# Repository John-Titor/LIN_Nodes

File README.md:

Firmware and PCB designs for various LIN network nodes intended for retrofitting older vehicles.

```
boards/
    Eagle schematic and PCB files.

common/
    Protocol definitions and generator.

Documentation/
    Datasheets for various parts used in the design.

lintool
    Host-side configuration tool. Talks to the usb_link hardware.

nodes/
    All of the nodes in this part of the tree are based on the Atmel ATTiny167.

    bl_core/
        LIN bootloader core, consumed by bl_installer.

    bl_installer/
        Bootloader installer; flashed onto a fresh board this will install the
        bootloader.

        The installed bootloader comes up on NAD 32 and can be flashed with lintool
        by explicitly supplying the node address and firmware file.

        lintool update -n 32 <path-to-fw-file>

        Only one node can be in this 'recovery' mode on the network when doing this.

    lib/
        Shared code.

    master/
        Network master node. Supports 7 switch-to-battery and 14 switch-to-ground
        inputs. 4 of the switch-to-ground inputs can also be 0-5V voltage inputs,
        with optional 2 or 16mA current sources for measuring resistive sensors.

    power_v3/
        5-output power switching node using Freescale smart high-side switches.
        Board limited to 5.5A, but code should work with the 10A device as well.
        Outputs support PWM, current monitoring, open- and short-circuit detection,
        overcurrent and overtemperature protection, etc.

    usb_link/
        USB bridge with support for configuration and node firmware updates.

```

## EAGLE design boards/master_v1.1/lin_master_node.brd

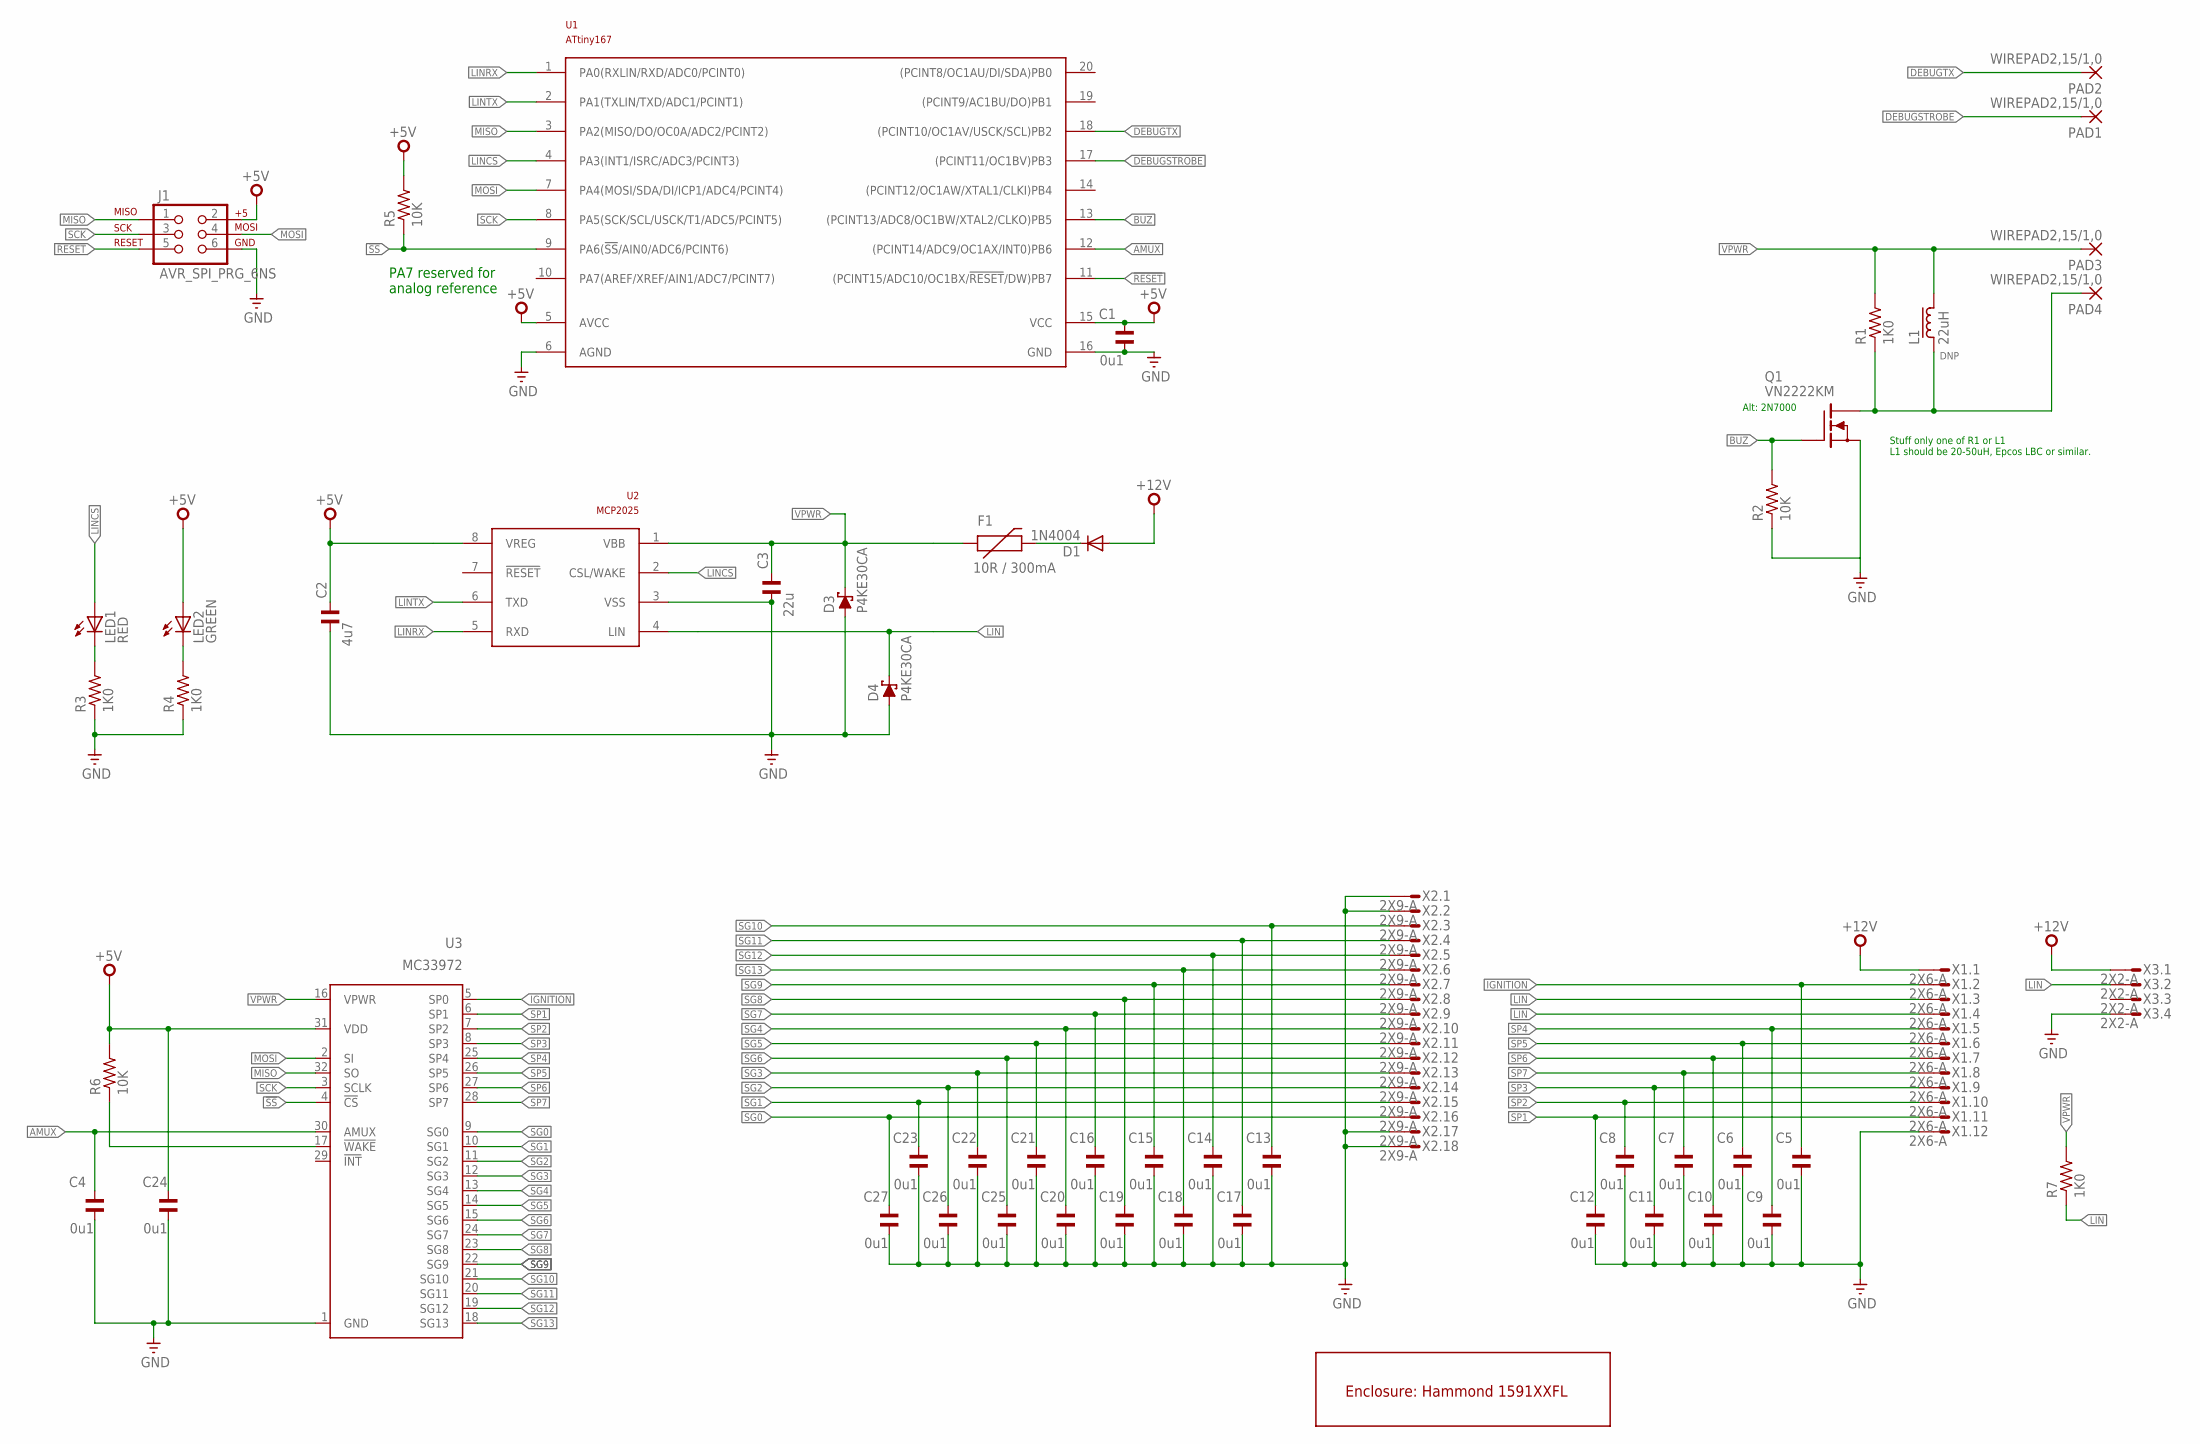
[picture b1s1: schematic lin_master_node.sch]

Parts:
C1, C4, C24: 0u1; C050-024X044; PARTNO FK28X7R1H104K
C2: 4u7; C050-024X044; PARTNO FK28X5R0J475K
C3: 22u; C050-024X044; PARTNO FK22X5R1E226M
C5, C6, C7, C8, C9, C10, C11, C12, C13, C14, C15, C16, C17, C18, C19, C20, C21, C22, C23, C25, C26, C27: 0u1; C0805K; PARTNO C2012X7R1H104K085AA
D1: 1N4004; DO41-10; PARTNO 1N4004-TP
D3, D4: P4KE30CA; DO41-10; PARTNO P4KE30CA
F1: 10R / 300mA; PTC; PARTNO CMF-RL10-0
J1: AVR_SPI_PRG_6NS; 2X3-NS
L1: 22uH; LBC15A
LED1: RED; LED3MM; PARTNO C4SMF-RJS-CT0W0BB2
LED2: GREEN; LED3MM; PARTNO C4SMF-GJS-CV0Y0792
PAD1, PAD2, PAD3, PAD4: WIREPAD2,15/1,0; 2,15/1,0
Q1: VN2222KM; TO237
R1, R3, R4, R7: 1K0; 0207/10; PARTNO CF14JT1K00
R2, R5, R6: 10K; 0207/10; PARTNO CF14JT10K0
U1: ATtiny167; SO20W; PARTNO ATTINY167-SU
U2: MCP2025; SO08; PARTNO MCP2025-500E/SN
U3: MC33972; SOIC32W; PARTNO MC33972ATEW
U$1: 1591XXAFL; PARTNO 1591XXAFLBK
X1: 2X6-A; 4-794618-2; PARTNO 4-794618-2
X2: 2X9-A; 4-794618-8; PARTNO 4-794618-8
X3: 2X2-A; 3-794618-4; PARTNO 3-794618-4

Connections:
!RESET: J1.5, U1.11 ((PCINT15/ADC10/OC1BX/!RESET!/DW)PB7)
!SS: R5.1, U1.9 (PA6(!SS!/AIN0/ADC6/PCINT6)), U3.4 (!CS)
+5V: C1.1, C2.1, C24.1, J1.2, LED2.A, R5.2, R6.2, U1.5 (AVCC), U1.15 (VCC), U2.8 (VREG), U3.31 (VDD)
+12V: D1.A, X1.1, X3.1
AMUX: C4.1, U1.12 ((PCINT14/ADC9/OC1AX/INT0)PB6), U3.30 (AMUX)
BUZ: Q1.2 (G), R2.2, U1.13 ((PCINT13/ADC8/OC1BW/XTAL2/CLKO)PB5)
DEBUGSTROBE: PAD1.1, U1.17 ((PCINT11/OC1BV)PB3)
DEBUGTX: PAD2.1, U1.18 ((PCINT10/OC1AV/USCK/SCL)PB2)
GND: C1.2, C2.2, C3.2, C4.2, C5.2, C6.2, C7.2, C8.2, C9.2, C10.2, C11.2, C12.2, C13.2, C14.2, C15.2, C16.2, C17.2, C18.2, C19.2, C20.2, C21.2, C22.2, C23.2, C24.2, C25.2, C26.2, C27.2, D3.A, D4.A, J1.6, Q1.3 (S), R2.1, R3.1, R4.1, U1.6 (AGND), U1.16 (GND), U2.3 (VSS), U3.1 (GND), X1.12, X2.1, X2.2, X2.17, X2.18, X3.4
IGNITION: C5.1, U3.5 (SP0), X1.2
LIN: D4.C, R7.1, U2.4 (LIN), X1.3, X1.4, X3.2
LINCS: LED1.A, U1.4 (PA3(INT1/ISRC/ADC3/PCINT3)), U2.2 (CSL/WAKE)
LINRX: U1.1 (PA0(RXLIN/RXD/ADC0/PCINT0)), U2.5 (RXD)
LINTX: U1.2 (PA1(TXLIN/TXD/ADC1/PCINT1)), U2.6 (TXD)
MISO: J1.1, U1.3 (PA2(MISO/DO/OC0A/ADC2/PCINT2)), U3.32 (SO)
MOSI: J1.4, U1.7 (PA4(MOSI/SDA/DI/ICP1/ADC4/PCINT4)), U3.2 (SI)
unnamed: LED1.K (C), R3.2
unnamed: R6.1, U3.17 (!WAKE)
unnamed: L1.1, PAD4.1, Q1.1 (D), R1.1
unnamed: LED2.K (C), R4.2
unnamed: D1.C, F1.P$2 (2)
SCK: J1.3, U1.8 (PA5(SCK/SCL/USCK/T1/ADC5/PCINT5)), U3.3 (SCLK)
SG0: C27.1, U3.9 (SG0), X2.16
SG1: C23.1, U3.10 (SG1), X2.15
SG2: C26.1, U3.11 (SG2), X2.14
SG3: C22.1, U3.12 (SG3), X2.13
SG4: C20.1, U3.13 (SG4), X2.10
SG5: C21.1, U3.14 (SG5), X2.11
SG6: C25.1, U3.15 (SG6), X2.12
SG7: C16.1, U3.24 (SG7), X2.9
SG8: C19.1, U3.23 (SG8), X2.8
SG9: C15.1, U3.22 (SG9), X2.7
SG10: C13.1, U3.21 (SG10), X2.3
SG11: C17.1, U3.20 (SG11), X2.4
SG12: C14.1, U3.19 (SG12), X2.5
SG13: C18.1, U3.18 (SG13), X2.6
SP1: C12.1, U3.6 (SP1), X1.11
SP2: C8.1, U3.7 (SP2), X1.10
SP3: C11.1, U3.8 (SP3), X1.9
SP4: C9.1, U3.25 (SP4), X1.5
SP5: C6.1, U3.26 (SP5), X1.6
SP6: C10.1, U3.27 (SP6), X1.7
SP7: C7.1, U3.28 (SP7), X1.8
VPWR: C3.1, D3.C, F1.P$1 (1), L1.2, PAD3.1, R1.2, R7.2, U2.1 (VBB), U3.16 (VPWR)

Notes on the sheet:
PA7 reserved for analog reference
Stuff only one of R1 or L1 L1 should be 20-50uH, Epcos LBC or similar.
Alt: 2N7000

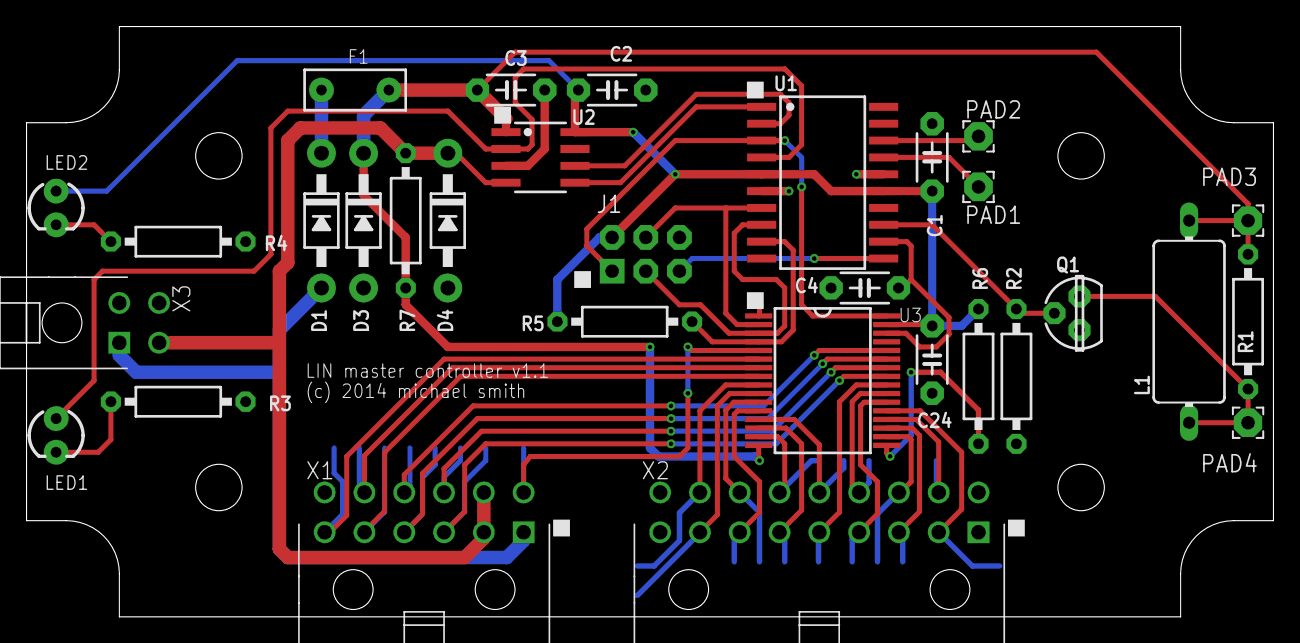
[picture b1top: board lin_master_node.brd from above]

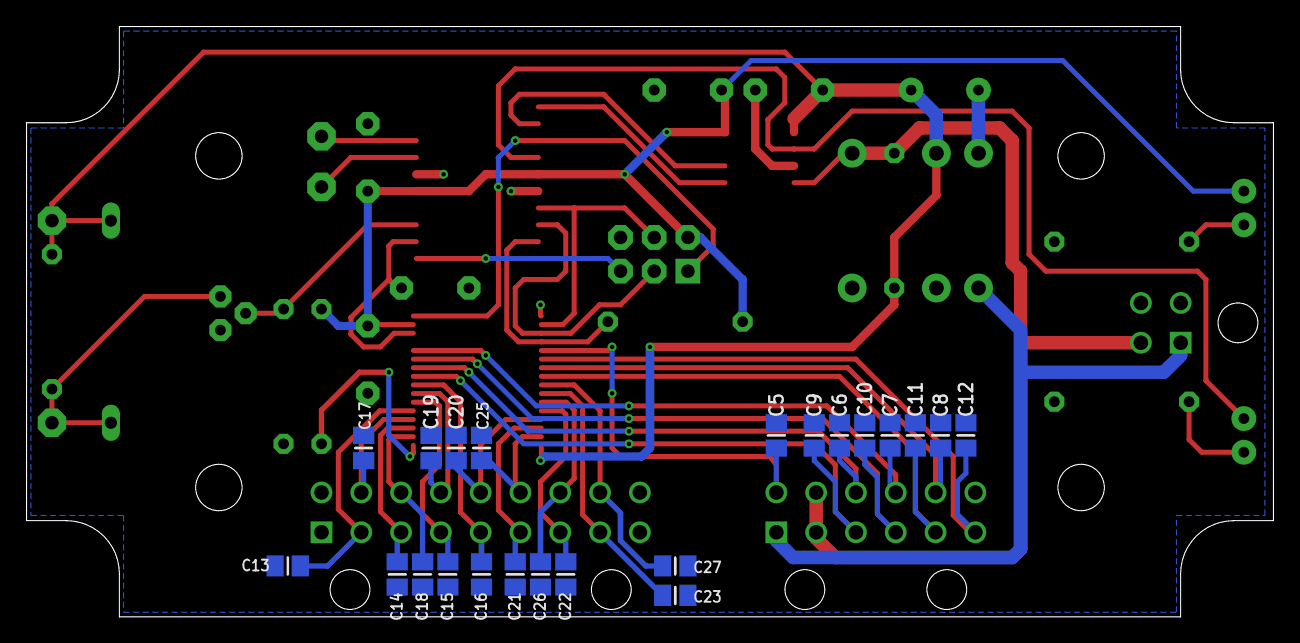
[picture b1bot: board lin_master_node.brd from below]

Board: 2 copper layers, 94.0 x 44.5 mm, 54 parts (22 on the bottom side), 44 nets.

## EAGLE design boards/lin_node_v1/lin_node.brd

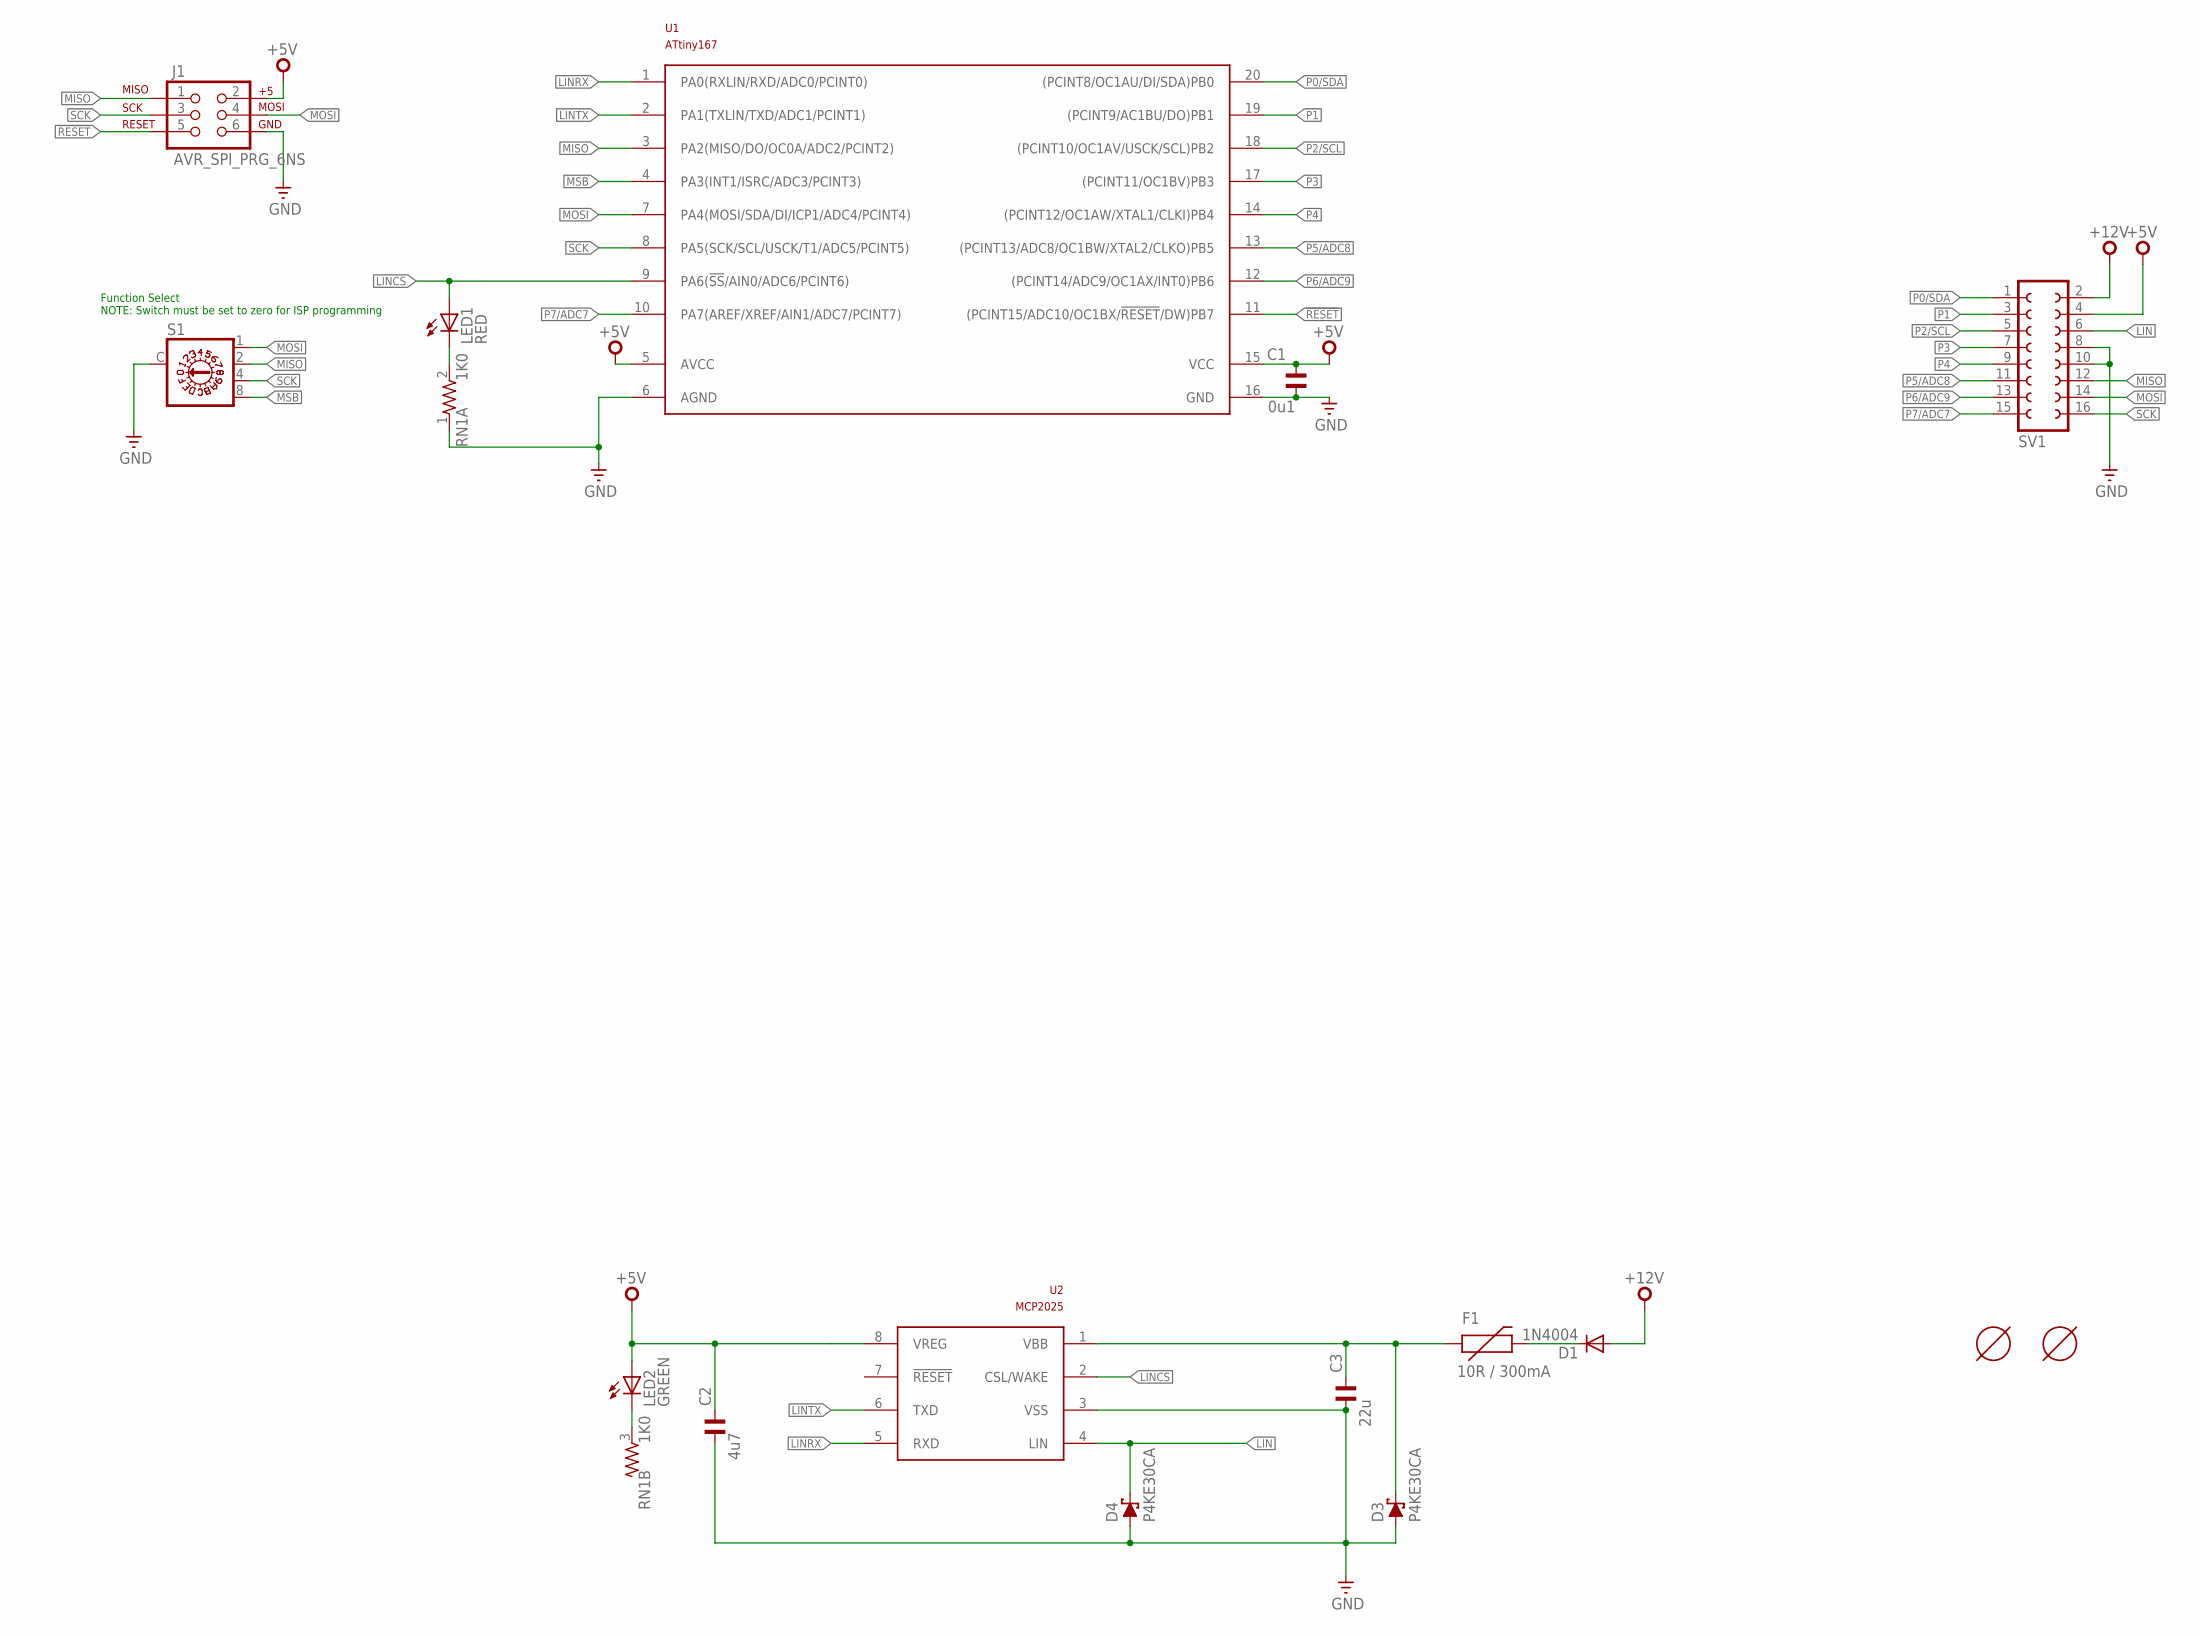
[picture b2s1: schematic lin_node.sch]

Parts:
C1: 0u1; C025-024X044; PARTNO FK28X7R1H104K
C2: 4u7; C050-024X044; PARTNO FK28X5R0J475K
C3: 22u; C050-024X044; PARTNO FK22X5R1E226M
D1: 1N4004; DO41-10; PARTNO 1N4004-TP
D3, D4: P4KE30CA; DO41-10; PARTNO P4KE30CA
F1: 10R / 300mA; PTC; PARTNO 600R150-RBZR
J1: AVR_SPI_PRG_6NS; 2X3-NS
LED1: RED; LED3MM; PARTNO C4SMF-RJS-CT0W0BB2
LED2: GREEN; LED3MM; PARTNO C4SMF-GJS-CV0Y0792
RN1: 1K0; SIL4; PARTNO 4604X-101-103LF
S1: P103; PARTNO SH-7050MC
SV1: FE08-2
U1: ATtiny167; SO20W; PARTNO ATTINY167-SU
U2: MCP2025; SO08; PARTNO MCP2025-500E/SN
U$1, U$2: MOUNT-HOLE3.1MM; MOUNT-HOLE3.1

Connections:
!RESET: J1.5, U1.11 ((PCINT15/ADC10/OC1BX/!RESET!/DW)PB7)
+5V: C1.1, C2.1, J1.2, LED2.A, SV1.4, U1.5 (AVCC), U1.15 (VCC), U2.8 (VREG)
+12V: D1.A, SV1.2
GND: C1.2, C2.2, C3.2, D3.A, D4.A, J1.6, RN1.1, S1.C, SV1.8, SV1.10, U1.6 (AGND), U1.16 (GND), U2.3 (VSS)
LIN: D4.C, SV1.6, U2.4 (LIN)
LINCS: LED1.A, U1.9 (PA6(!SS!/AIN0/ADC6/PCINT6)), U2.2 (CSL/WAKE)
LINRX: U1.1 (PA0(RXLIN/RXD/ADC0/PCINT0)), U2.5 (RXD)
LINTX: U1.2 (PA1(TXLIN/TXD/ADC1/PCINT1)), U2.6 (TXD)
MISO: J1.1, S1.2, SV1.12, U1.3 (PA2(MISO/DO/OC0A/ADC2/PCINT2))
MOSI: J1.4, S1.1, SV1.14, U1.7 (PA4(MOSI/SDA/DI/ICP1/ADC4/PCINT4))
MSB: S1.8, U1.4 (PA3(INT1/ISRC/ADC3/PCINT3))
unnamed: C3.1, D3.C, F1.P$1 (1), U2.1 (VBB)
unnamed: LED1.K (C), RN1.2
unnamed: LED2.K (C), RN1.3 (2)
unnamed: D1.C, F1.P$2 (2)
P0/SDA: SV1.1, U1.20 ((PCINT8/OC1AU/DI/SDA)PB0)
P1: SV1.3, U1.19 ((PCINT9/AC1BU/DO)PB1)
P2/SCL: SV1.5, U1.18 ((PCINT10/OC1AV/USCK/SCL)PB2)
P3: SV1.7, U1.17 ((PCINT11/OC1BV)PB3)
P4: SV1.9, U1.14 ((PCINT12/OC1AW/XTAL1/CLKI)PB4)
P5/ADC8: SV1.11, U1.13 ((PCINT13/ADC8/OC1BW/XTAL2/CLKO)PB5)
P6/ADC9: SV1.13, U1.12 ((PCINT14/ADC9/OC1AX/INT0)PB6)
P7/ADC7: SV1.15, U1.10 (PA7(AREF/XREF/AIN1/ADC7/PCINT7))
SCK: J1.3, S1.4, SV1.16, U1.8 (PA5(SCK/SCL/USCK/T1/ADC5/PCINT5))

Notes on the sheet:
Function Select NOTE: Switch must be set to zero for ISP programming

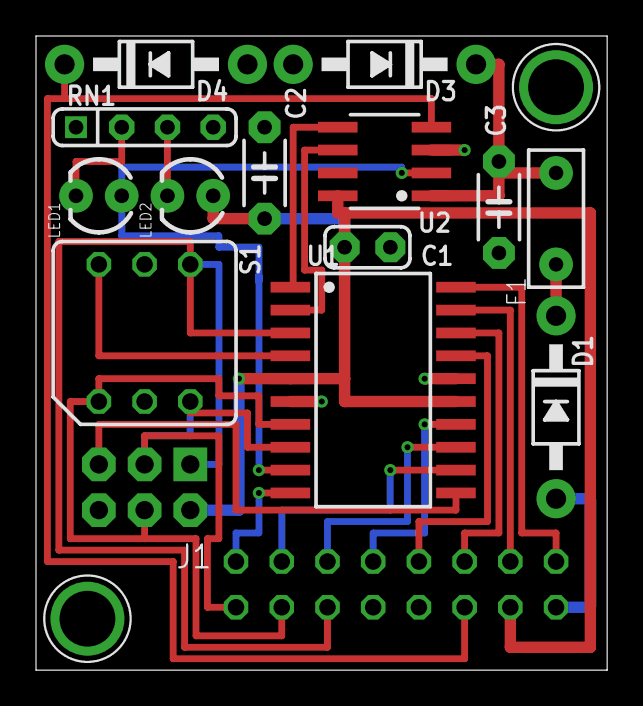
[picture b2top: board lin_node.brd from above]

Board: 2 copper layers, 31.7 x 35.2 mm, 17 parts (1 on the bottom side), 24 nets.

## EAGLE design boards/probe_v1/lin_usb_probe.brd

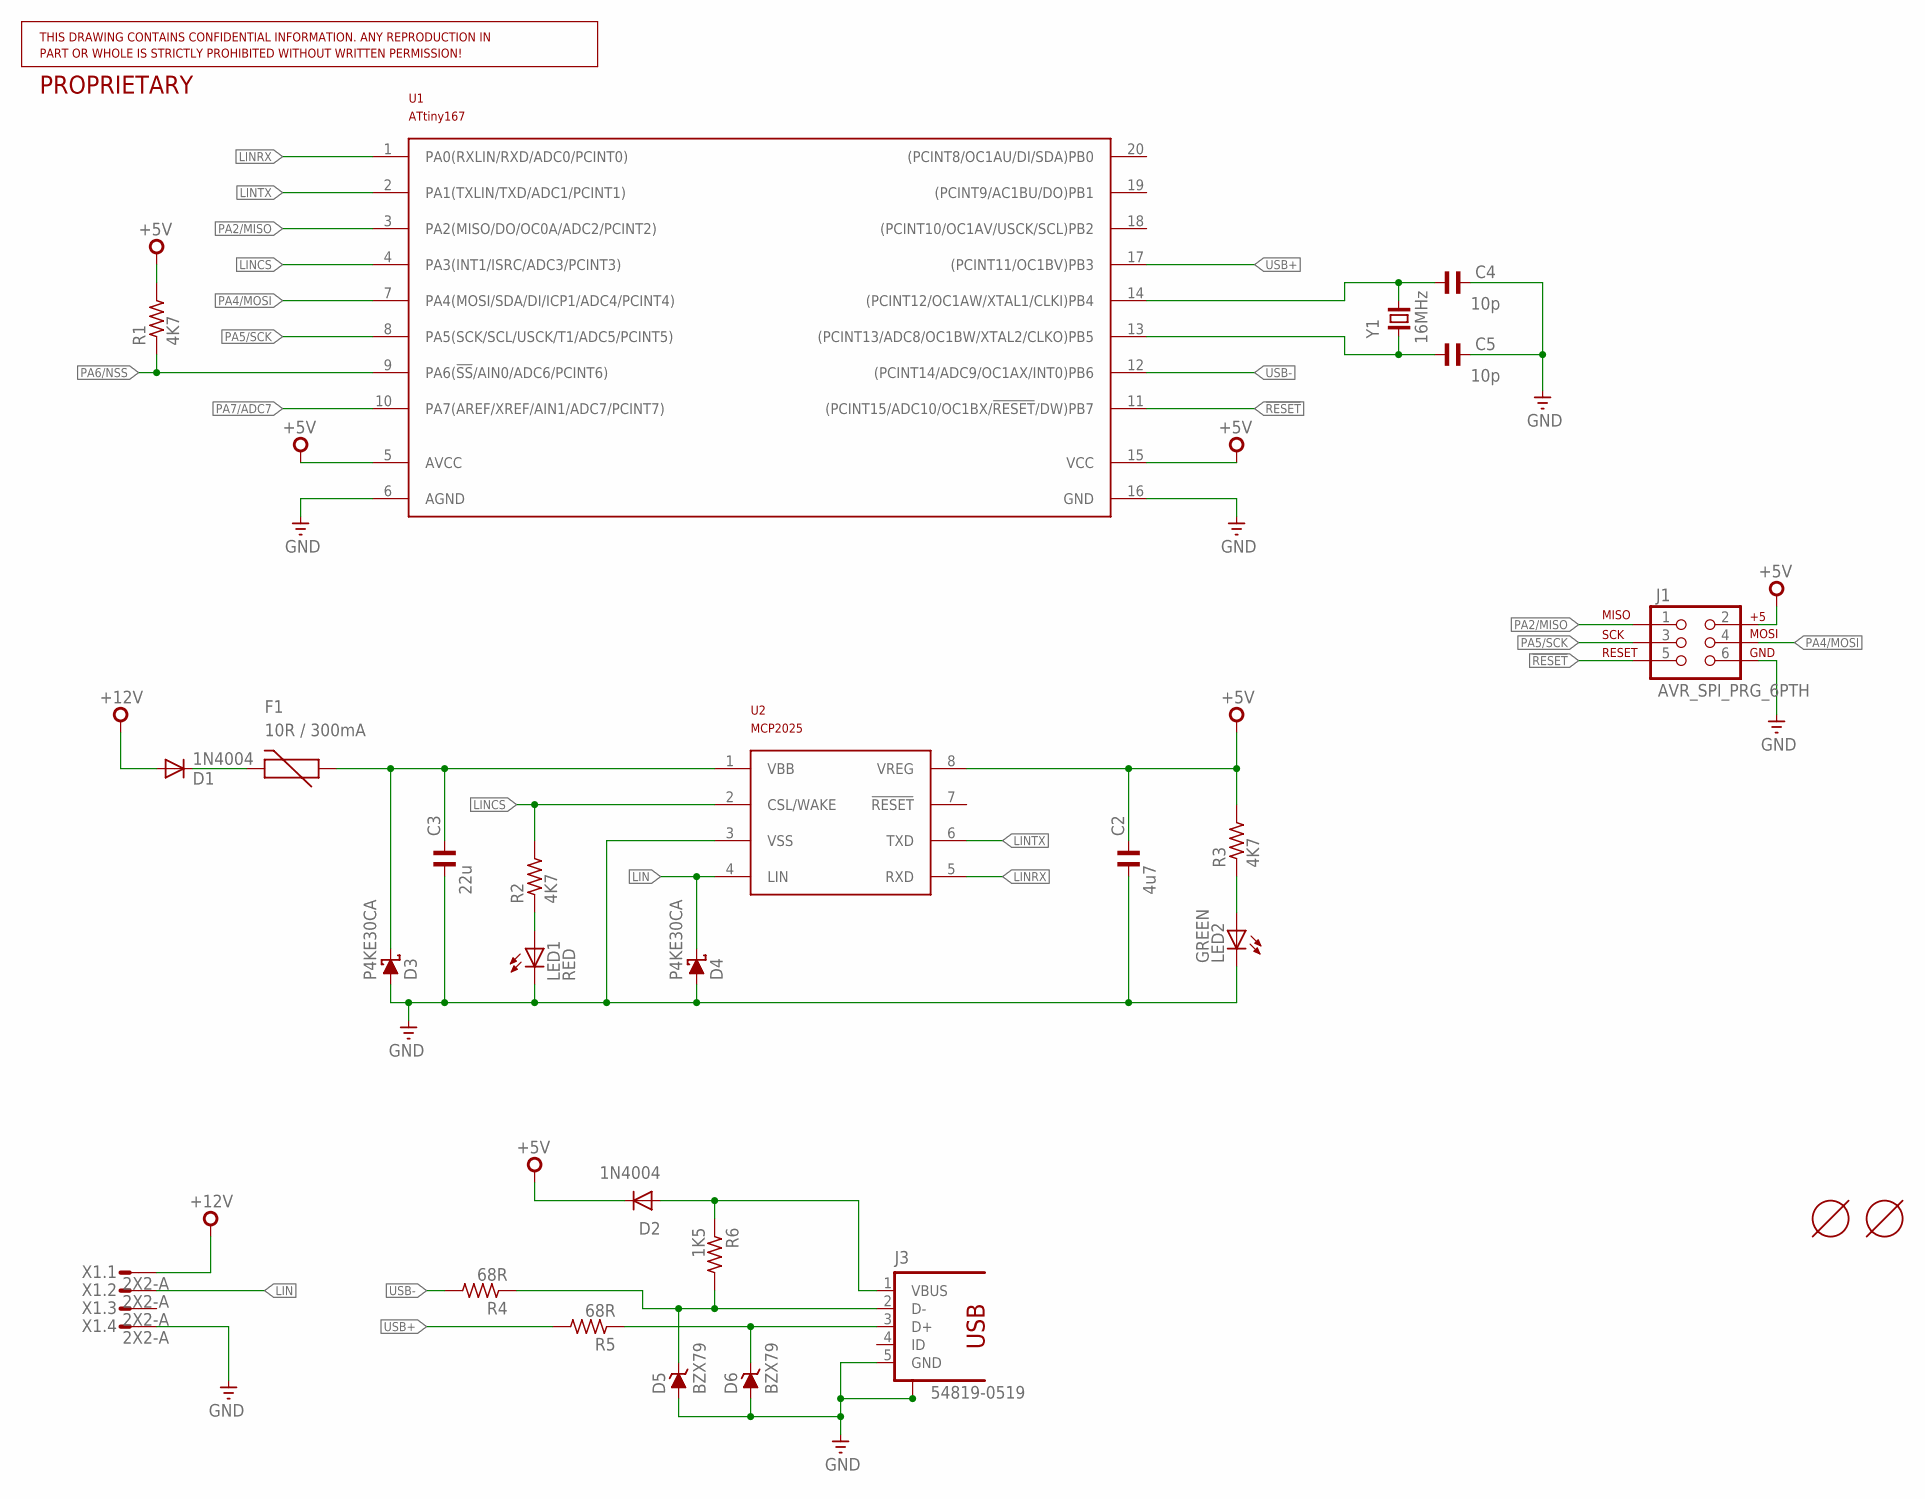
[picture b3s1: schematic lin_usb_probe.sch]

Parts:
C2: 4u7; C050-024X044; PARTNO GRM21BR71A475KA73K
C3: 22u; C050-024X044; PARTNO C2012X5R1V226M125AC
C4, C5: 10p; C025-024X044
D1: 1N4004; DO41-10; PARTNO 1N4004-TP
D2: 1N4004; DO41-10
D3, D4: P4KE30CA; DO41-10; PARTNO P4KE30CA
D5, D6: BZX79; DO35Z10
F1: 10R / 300mA; PTC; PARTNO 600R150-RBZR
J1: AVR_SPI_PRG_6PTH; 2X3
J3: 54819-0519
LED1: RED; LED3MM; PARTNO C4SMF-RJS-CT0W0BB2
LED2: GREEN; LED3MM; PARTNO C4SMF-GJS-CV0Y0792
R1, R2, R3: 4K7; 0207/10; PARTNO ERJ-6GEYJ472V
R4, R5: 68R; 0207/10; PARTNO ERJ-6GEYJ472V
R6: 1K5; 0207/10; PARTNO ERJ-6GEYJ472V
U1: ATtiny167; TSSOP20; PARTNO ATTINY167-A15XZ
U2: MCP2025; SO08; PARTNO MCP2025-500E/SN
U$1, U$2: MOUNT-HOLE3.1MM; MOUNT-HOLE3.1
X1: 2X2-A; 3-794618-4
Y1: 16MHz; HC49/S

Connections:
!RESET: J1.5, U1.11 ((PCINT15/ADC10/OC1BX/!RESET!/DW)PB7)
+5V: C2.1, D2.C, J1.2, R1.2, R3.2, U1.5 (AVCC), U1.15 (VCC), U2.8 (VREG)
+12V: D1.A, X1.1
GND: C2.2, C3.2, C4.1, C5.1, D3.A, D4.A, D5.A, D6.A, J1.6, J3.5 (GND), J3.S1, J3.S2, LED1.K (C), LED2.K (C), U1.6 (AGND), U1.16 (GND), U2.3 (VSS), X1.4
LIN: D4.C, U2.4 (LIN), X1.2
LINCS: R2.2, U1.4 (PA3(INT1/ISRC/ADC3/PCINT3)), U2.2 (CSL/WAKE)
LINRX: U1.1 (PA0(RXLIN/RXD/ADC0/PCINT0)), U2.5 (RXD)
LINTX: U1.2 (PA1(TXLIN/TXD/ADC1/PCINT1)), U2.6 (TXD)
unnamed: C4.2, U1.14 ((PCINT12/OC1AW/XTAL1/CLKI)PB4), Y1.2
unnamed: C3.1, D3.C, F1.P$1 (1), U2.1 (VBB)
unnamed: LED1.A, R2.1
unnamed: LED2.A, R3.1
unnamed: D1.C, F1.P$2 (2)
unnamed: D6.C, J3.3 (D+), R5.1
unnamed: D5.C, J3.2 (D-), R4.1, R6.2
unnamed: D2.A, J3.1 (VBUS), R6.1
unnamed: C5.2, U1.13 ((PCINT13/ADC8/OC1BW/XTAL2/CLKO)PB5), Y1.1
PA2/MISO: J1.1, U1.3 (PA2(MISO/DO/OC0A/ADC2/PCINT2))
PA4/MOSI: J1.4, U1.7 (PA4(MOSI/SDA/DI/ICP1/ADC4/PCINT4))
PA5/SCK: J1.3, U1.8 (PA5(SCK/SCL/USCK/T1/ADC5/PCINT5))
PA6/NSS: R1.1, U1.9 (PA6(!SS!/AIN0/ADC6/PCINT6))
PA7/ADC7: U1.10 (PA7(AREF/XREF/AIN1/ADC7/PCINT7))
USB+: R5.2, U1.17 ((PCINT11/OC1BV)PB3)
USB-: R4.2, U1.12 ((PCINT14/ADC9/OC1AX/INT0)PB6)

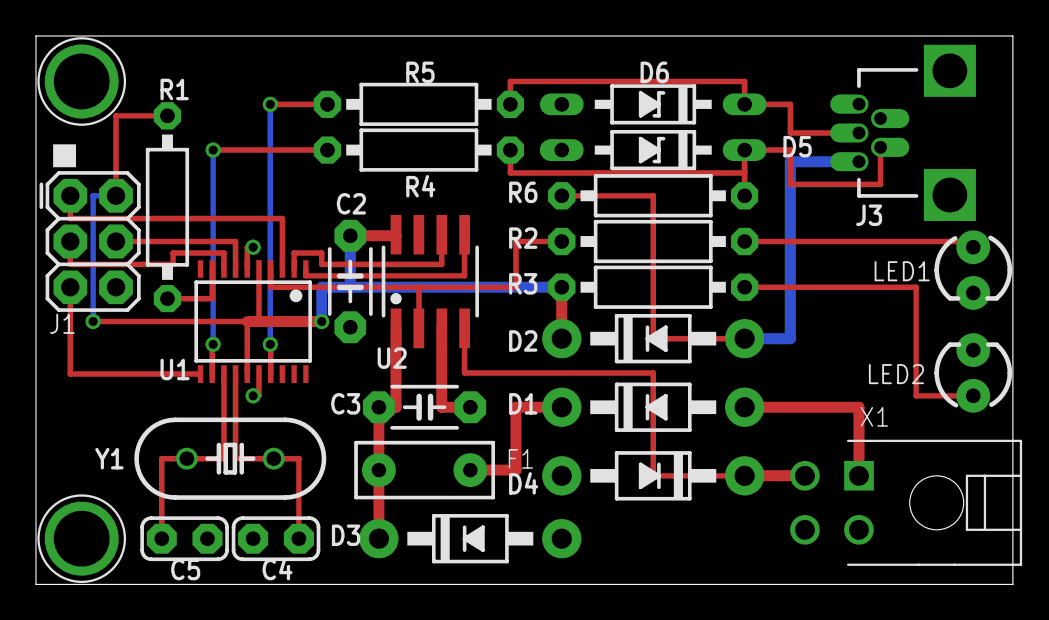
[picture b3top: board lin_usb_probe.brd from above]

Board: 2 copper layers, 54.3 x 30.5 mm, 27 parts (0 on the bottom side), 23 nets.

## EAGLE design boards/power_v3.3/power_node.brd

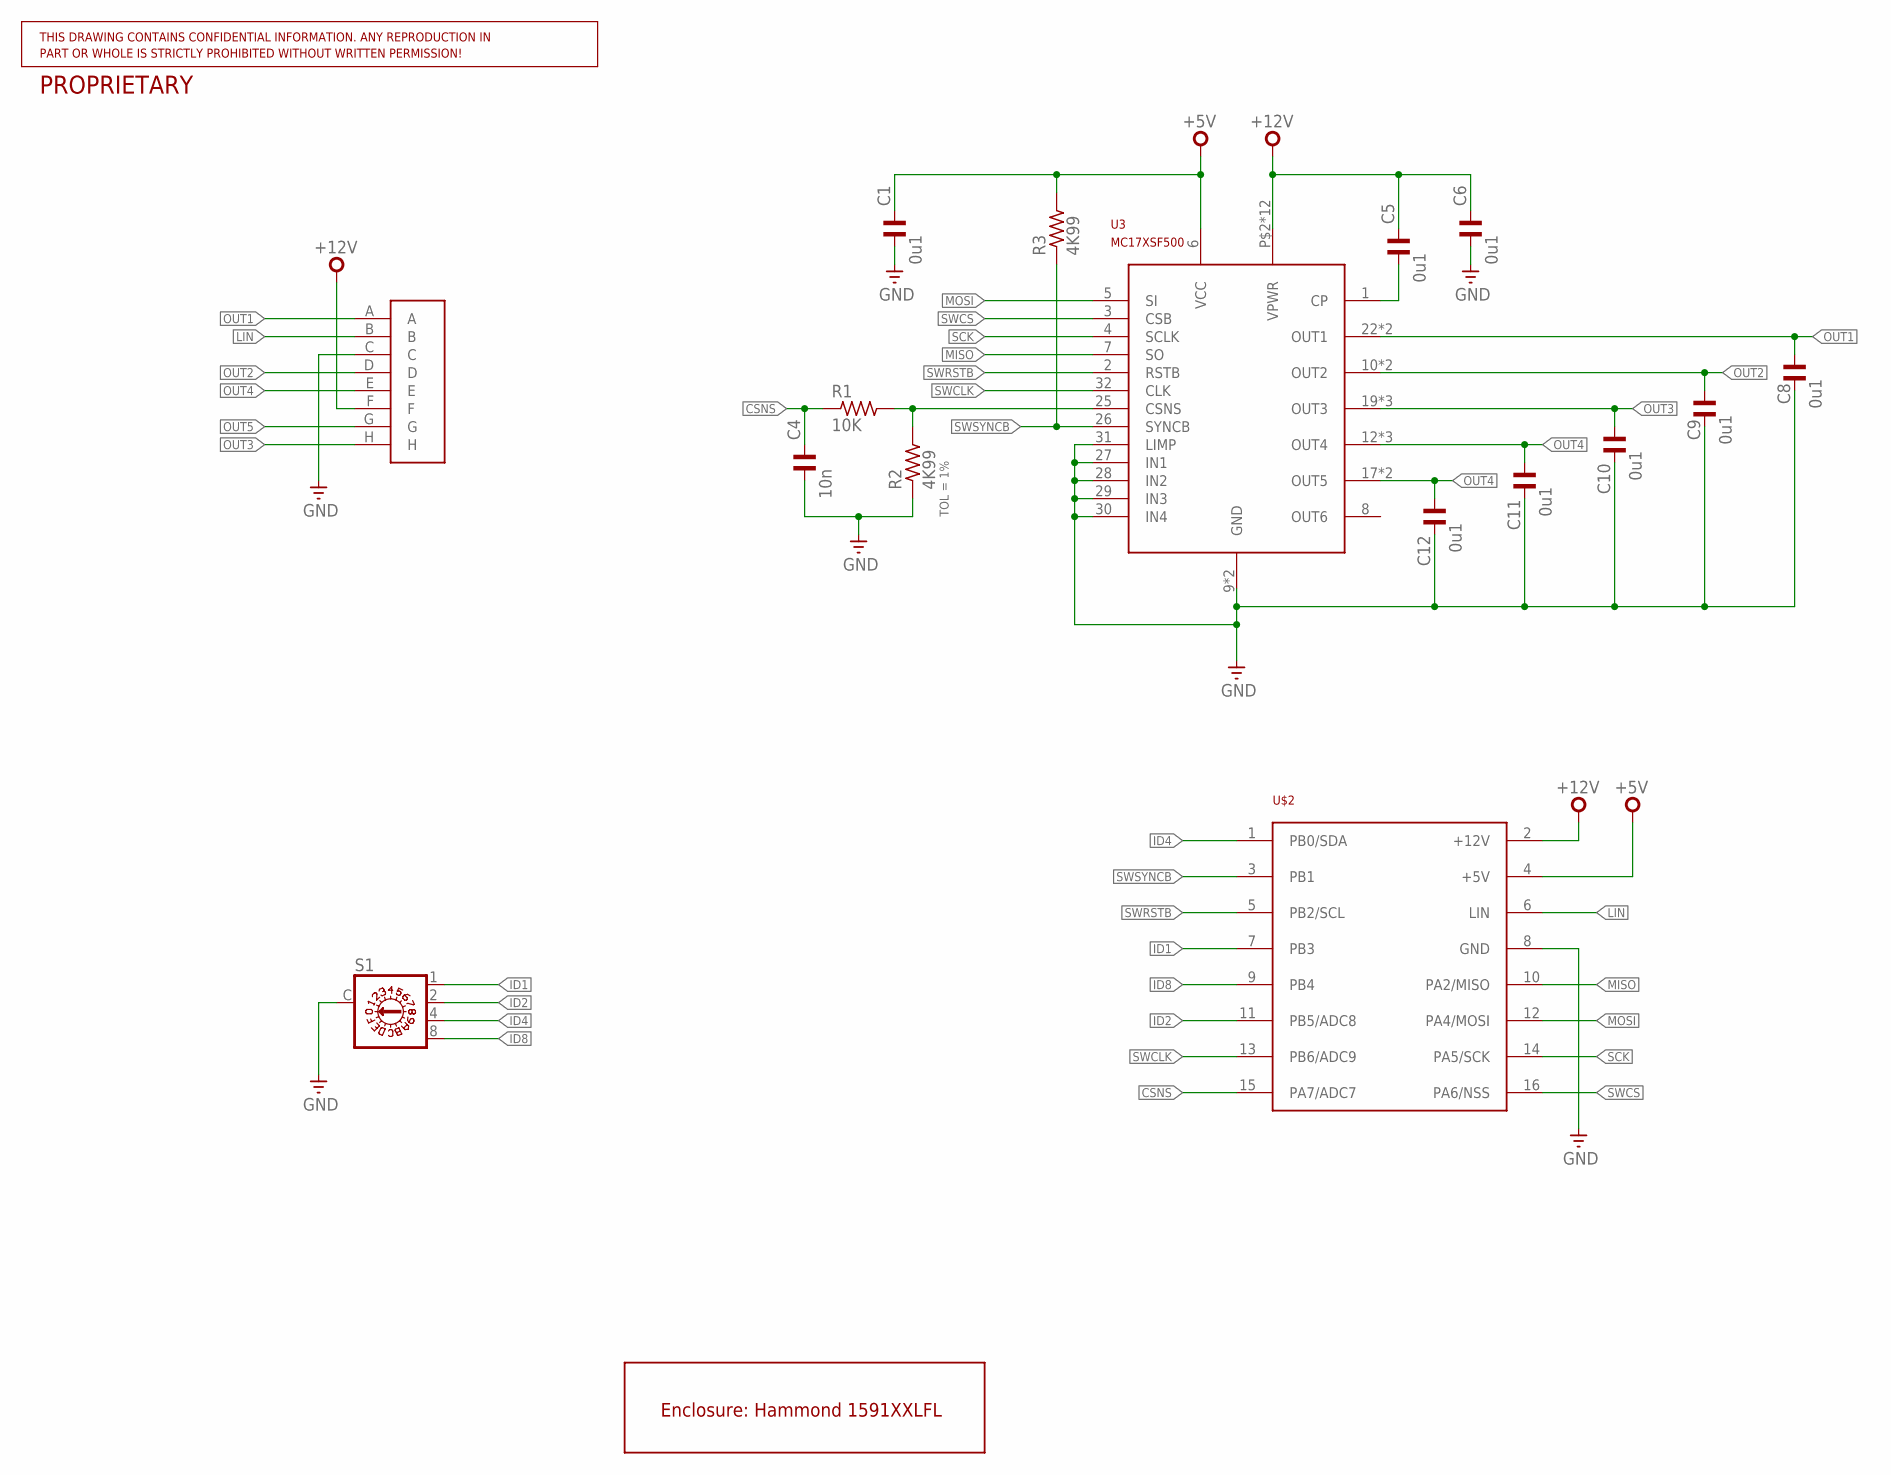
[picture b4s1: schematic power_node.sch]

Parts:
C1, C5, C6: 0u1; C0805K; PARTNO FK28X7R1H104K
C4: 10n; C0805K; PARTNO FK18X7R1H103K
C8, C9, C10, C11, C12: 0u1; C0805K; PARTNO C1608X7R1H104M080AA
J2: 12146734; PARTNO 12146724-B
R1: 10K; R0805W; PARTNO CF14JT10K0
R2, R3: 4K99; R0805W; PARTNO MFR-25FBF52-4K99
S1: P103; PARTNO SH-7050MC
U3: MC17XSF500; SOIC32W-EP; PARTNO MC17XSF500EK
U$1: 1591XXLFL; PARTNO 1591XXLFLBK
U$2: LIN_NODEHORIZ; LIN_NODE

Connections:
+5V: C1.1, R3.2, U3.6 (VCC), U$2.4 (+5V)
+12V: C5.1, C6.1, J2.F, U3.P$2 (VPWR), U3.P$3 (VPWR), U3.P$4 (VPWR), U3.P$5 (VPWR), U3.P$6 (VPWR), U3.P$7 (VPWR), U3.P$8 (VPWR), U3.P$9 (VPWR), U3.P$10 (VPWR), U3.P$11 (VPWR), U3.P$12 (VPWR), U3.P$13 (VPWR), U$2.2 (+12V)
CSNS: C4.1, R1.1, U$2.15 (PA7/ADC7)
GND: C1.2, C4.2, C6.2, C8.2, C9.2, C10.2, C11.2, C12.2, J2.C, R2.1, S1.C, U3.9 (GND), U3.24 (GND), U3.27 (IN1), U3.28 (IN2), U3.29 (IN3), U3.30 (IN4), U3.31 (LIMP), U$2.8 (GND)
ID1: S1.1, U$2.7 (PB3)
ID2: S1.2, U$2.11 (PB5/ADC8)
ID4: S1.4, U$2.1 (PB0/SDA)
ID8: S1.8, U$2.9 (PB4)
LIN: J2.B, U$2.6 (LIN)
MISO: U3.7 (SO), U$2.10 (PA2/MISO)
MOSI: U3.5 (SI), U$2.12 (PA4/MOSI)
unnamed: C5.2, U3.1 (CP)
unnamed: R1.2, R2.2, U3.25 (CSNS)
OUT1: C8.1, J2.A, U3.22 (OUT1), U3.23 (OUT1)
OUT2: C9.1, J2.D, U3.10 (OUT2), U3.11 (OUT2)
OUT3: C10.1, J2.H, U3.19 (OUT3), U3.20 (OUT3), U3.21 (OUT3)
OUT4: C11.1, J2.E, U3.12 (OUT4), U3.13 (OUT4), U3.14 (OUT4)
OUT5: C12.1, J2.G, U3.17 (OUT5), U3.18 (OUT5)
SCK: U3.4 (SCLK), U$2.14 (PA5/SCK)
SWCLK: U3.32 (CLK), U$2.13 (PB6/ADC9)
SWCS: U3.3 (CSB), U$2.16 (PA6/NSS)
SWRSTB: U3.2 (RSTB), U$2.5 (PB2/SCL)
SWSYNCB: R3.1, U3.26 (SYNCB), U$2.3 (PB1)

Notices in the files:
nodes/usb_link/micronucleus/configuration/t167_lin/bootloaderconfig.h:
License: GNU GPL v2 (see License.txt
boards/lin_node_v1/lin_node.brd:
©2014 michael smith
boards/master_v1.1/lin_master_node.brd:
(c) 2014 michael smith
boards/power_v3.3/power_node.brd:
(c)2014
boards/probe_v1/lin_usb_probe.brd:
©2015 michael smith
